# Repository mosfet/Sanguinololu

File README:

http://reprap.org/wiki/Sanguinololu

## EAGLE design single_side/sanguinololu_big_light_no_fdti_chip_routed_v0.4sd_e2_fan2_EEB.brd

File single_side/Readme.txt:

This is single side version of the board. 
-There are significant electrical changes
-12V needs to be distributed by thick jumper wires
-there are two GND bridges marked with red (top layer)
-serial jumper needs GND/power as jumper wires

features:
-large, single sided board designed for direct milling with f.e. "cyclone pcb factory"
-EEB (Extruder, Extruder, Bed) mosfet setup
-pwm on PB4 with bipolar key transistor for fan PWM (bd139)
-additional heater thermistor input
-built-in SD card reader header( for printing with auto0.g)
-removed FDTI - use esp8266 or just TTL serial cable instead, or bt module - designed with old android phone as display in mind
-there is i2c header for display and 3 pins left for encoder in case you Really need old clunky LCD
-additional E1 axis 
-better thermal design, large traces

TODO : 
-schematic needs tidy up actions. 
-untested yet. prints/etches ok with 0.22mm tool. 
-normalize drill sizes

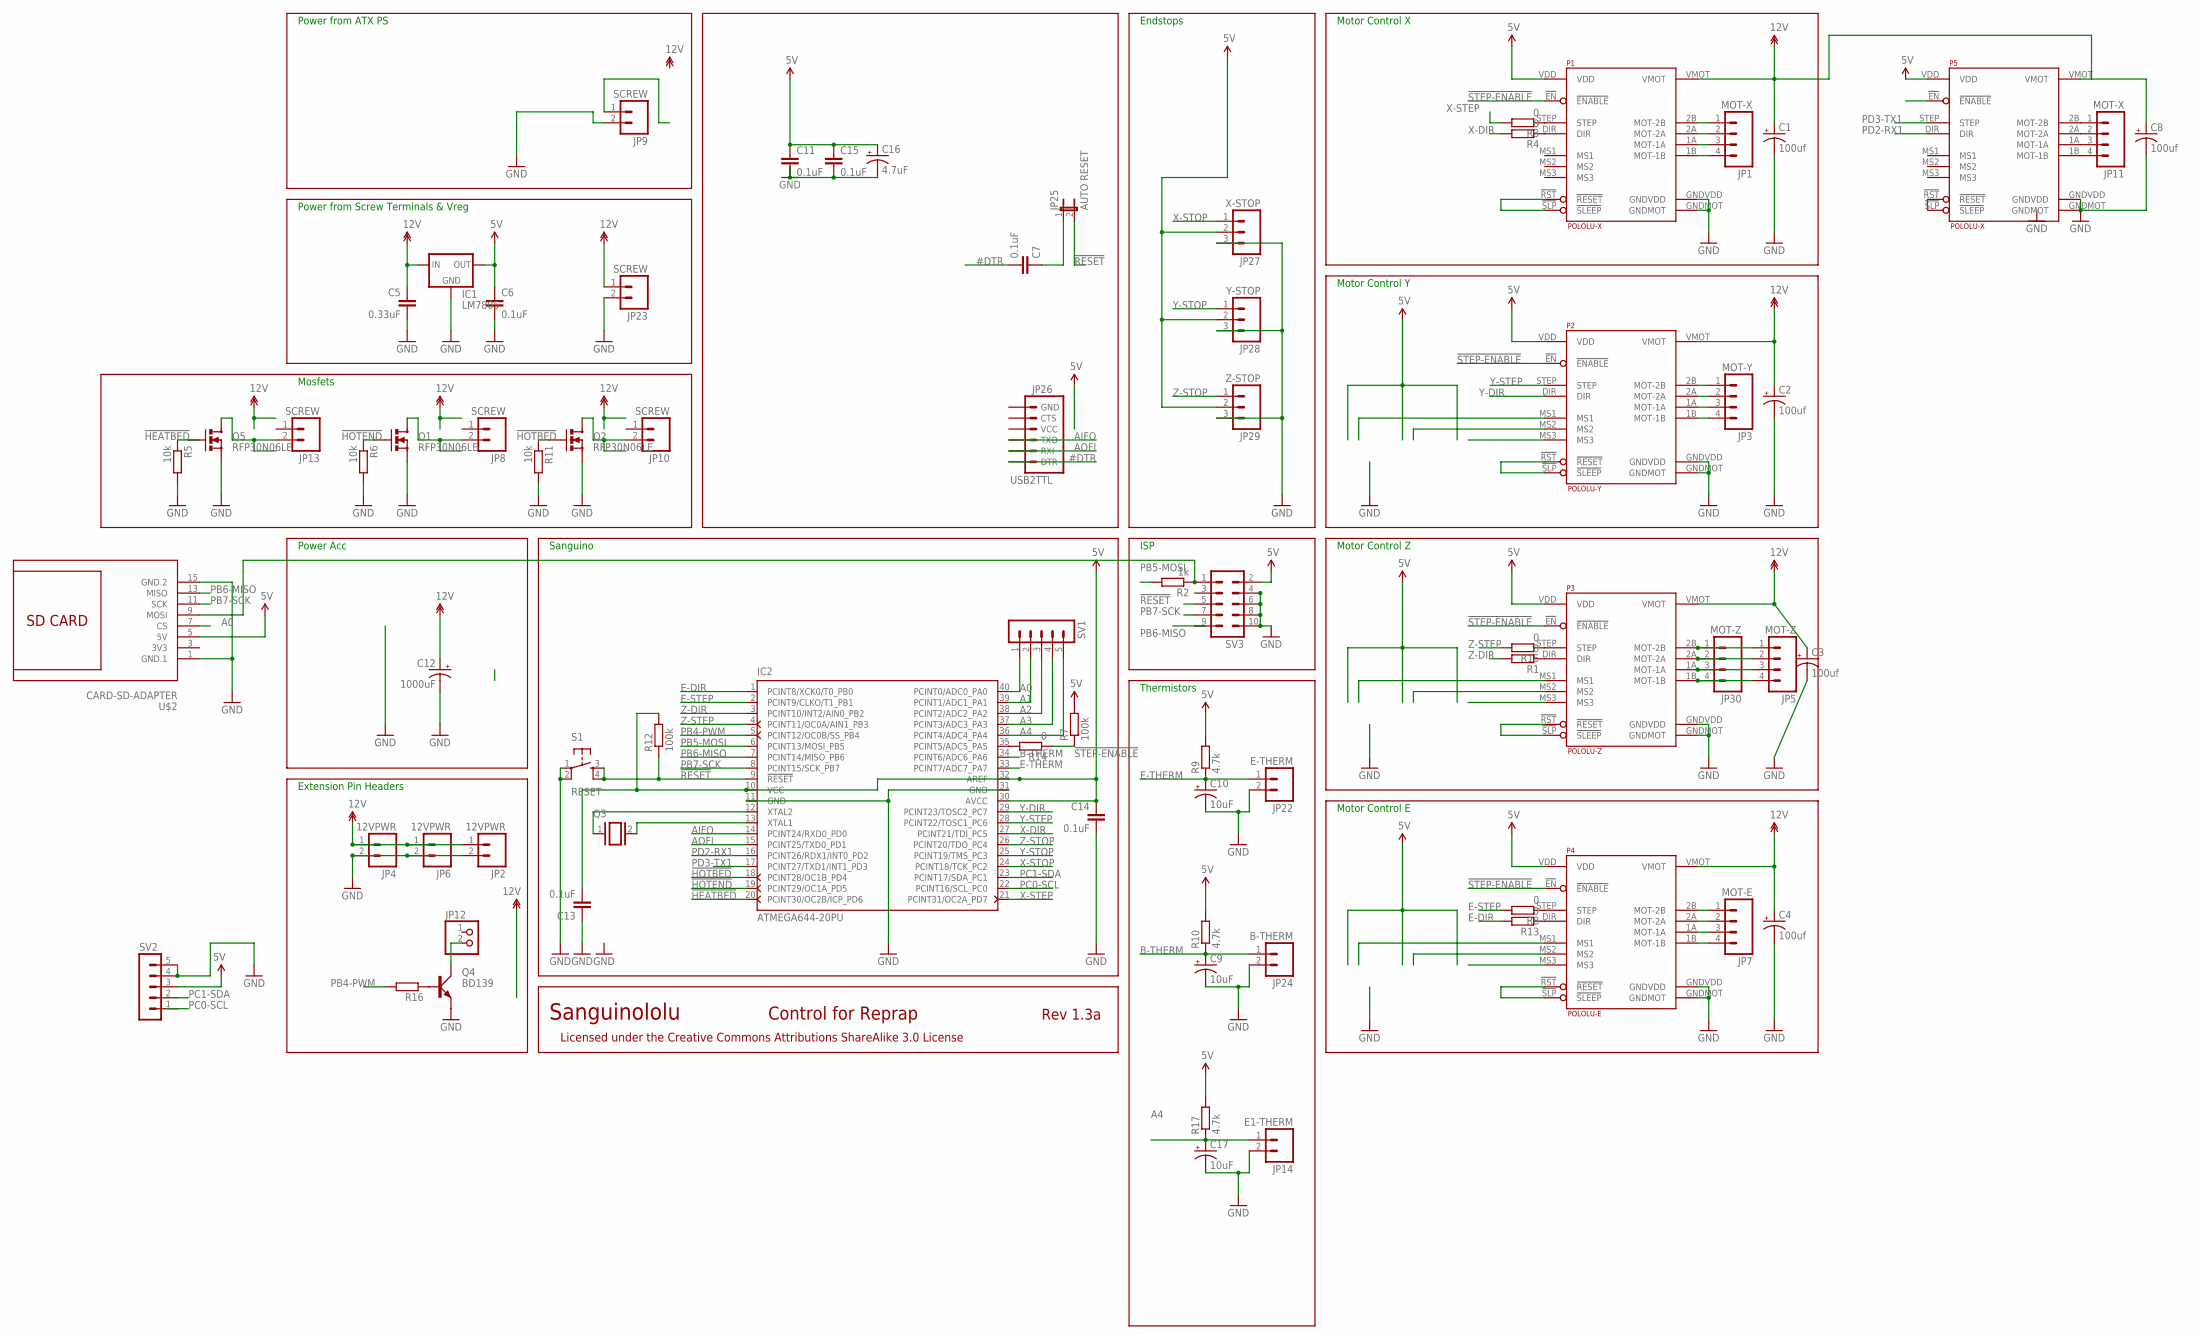
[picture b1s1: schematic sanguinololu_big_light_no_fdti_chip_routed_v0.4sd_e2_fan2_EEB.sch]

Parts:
C1, C2, C3, C4, C8: 100uf; CPOL-RADIAL-100UF-25V
C5: 0.33uF; CAP-PTH-SMALL2
C6, C13, C14: 0.1uF; CAP-PTH-SMALL2
C7: 0.1uF; C075-032X103
C9, C10, C17: 10uF; CPOL-RADIAL-10UF-25V
C11, C15: 0.1uF; C5B3
C12: 1000uF; CPOL-RADIAL-1000UF-25V
C16: 4.7uF; CPOL-RADIAL-10UF-25V
IC1: LM7805; 78XXL-CUSTOM
IC2: ATMEGA644-20PU; DIL40
JP1, JP11: MOT-X; MOLEX-1X4
JP2, JP4, JP6: 12VPWR; MOLEX-1X2
JP3: MOT-Y; MOLEX-1X4
JP5, JP30: MOT-Z; MOLEX-1X4
JP7: MOT-E; MOLEX-1X4
JP8, JP9, JP10, JP13, JP23: SCREW; SCREWTERMINAL-5MM-2
JP12: PINHD-1X2; 1X02
JP14: E1-THERM; 1X02
JP22: E-THERM; 1X02
JP24: B-THERM; 1X02
JP25: AUTO RESET; 1X02
JP26: USB2TTL; 1X06
JP27: X-STOP; MOLEX-1X3
JP28: Y-STOP; MOLEX-1X3
JP29: Z-STOP; MOLEX-1X3
P1, P5: POLOLU-X; POLOLU-ALLEGRO-PTH
P2: POLOLU-Y; POLOLU-ALLEGRO-PTH
P3: POLOLU-Z; POLOLU-ALLEGRO-PTH
P4: POLOLU-E; POLOLU-ALLEGRO-PTH
Q1, Q2, Q5: RFP30N06LE; TO220V
Q3: XTAL/S; QS
Q4: BD139; TO126AV
R1, R3, R4, R8, R13, R14, R15: 0; 0207/15
R2: 1k; 0207/15
R5, R6, R11: 10k; 0207/7
R7, R12: 100k; 0207/7
R9, R10, R17: 4.7k; 0207/7
R16: R-EU_0204/2V; 0204V
S1: RESET; TACTILE-PTH
SV1, SV2: MA05-1
SV3: MA05-2
U$2: CARD-SD-ADAPTER

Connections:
3V3: U$2.3 (3V3)
5V: C6.1, C11.1, C13.2, C14.1, C15.1, C16.1 (+), IC1.OUT, IC2.10 (VCC), IC2.30 (AVCC), IC2.32 (AREF), JP27.2, JP28.2, JP29.2, P1.VDD, P2.VDD, P3.VDD, P4.VDD, P5.VDD, R7.2, R9.2, R10.2, R12.2, R17.2, SV2.3, SV3.2, U$2.5 (5V)
12V: C1.1 (+), C2.1 (+), C3.1 (+), C4.1 (+), C5.1, C8.1 (+), C12.1 (+), IC1.IN, JP2.1, JP4.1, JP6.1, JP23.1, P1.VMOT, P2.VMOT, P3.VMOT, P4.VMOT, P5.VMOT
!FTDI-RESET: C7.1, JP25.1
!HEATBED: IC2.20 (PCINT30/OC2B/ICP_PD6), Q5.1 (G), R5.1
!HOTBED: IC2.18 (PCINT28/OC1B_PD4), Q2.1 (G), R11.1
!HOTEND: IC2.19 (PCINT29/OC1A_PD5), Q1.1 (G), R6.1
!RESET: IC2.9 (!RESET), JP25.2, R12.1, S1.3, S1.4, SV3.5
!STEP-ENABLE: P1.!EN (!ENABLE), P2.!EN (!ENABLE), P3.!EN (!ENABLE), P4.!EN (!ENABLE), P5.!EN (!ENABLE), R7.1, R14.1
#DTR: C7.2, JP26.1 (DTR)
A0: IC2.40 (PCINT0/ADC0_PA0), SV1.1, U$2.7 (CS)
A1: IC2.39 (PCINT1/ADC1_PA1), SV1.2
A2: IC2.38 (PCINT2/ADC2_PA2), SV1.3
A3: IC2.37 (PCINT3/ADC3_PA3), SV1.4
A4: C17.1 (+), IC2.36 (PCINT4/ADC4_PA4), JP14.1, R17.1, SV1.5
AIFO: IC2.14 (PCINT24/RXD0_PD0), JP26.3 (TXO)
AOFI: IC2.15 (PCINT25/TXD0_PD1), JP26.2 (RXI)
B-THERM: C9.1 (+), IC2.34 (PCINT6/ADC6_PA6), JP24.1, R10.1
E-DIR: IC2.1 (PCINT8/XCK0/T0_PB0), R13.2
E-MOT-1A: JP7.3, P4.1A (MOT-1A)
E-MOT-1B: JP7.4, P4.1B (MOT-1B)
E-MOT-2A: JP7.2, P4.2A (MOT-2A)
E-MOT-2B: JP7.1, P4.2B (MOT-2B)
E-MS1: P4.MS1
E-MS2: P4.MS2
E-MS3: P4.MS3
E-RESETSLEEP: P4.!RST (!RESET), P4.!SLP (!SLEEP)
E-STEP: IC2.2 (PCINT9/CLKO/T1_PB1), R8.2
E-THERM: C10.1 (+), IC2.33 (PCINT7/ADC7_PA7), JP22.1, R9.1
GND: C1.2 (-), C2.2 (-), C3.2 (-), C4.2 (-), C5.2, C6.2, C8.2 (-), C9.2 (-), C10.2 (-), C11.2, C12.2 (-), C13.1, C14.2, C15.2, C16.2 (-), C17.2 (-), IC1.GND, IC2.11 (GND), IC2.31 (GND), JP2.2, JP4.2, JP6.2, JP9.2, JP14.2, JP22.2, JP23.2, JP24.2, JP27.3, JP28.3, JP29.3, P1.GNDMOT, P1.GNDVDD, P2.GNDMOT, P2.GNDVDD, P3.GNDMOT, P3.GNDVDD, P4.GNDMOT, P4.GNDVDD, P5.GNDMOT, P5.GNDVDD, Q1.3 (S), Q2.3 (S), Q4.E, Q5.3 (S), R5.2, R6.2, R11.2, S1.1, S1.2, SV2.4, SV2.5, SV3.4, SV3.6, SV3.8, SV3.10, U$2.1 (GND.1), U$2.15 (GND.2)
HOTBED-GND: JP10.2, Q2.2 (D)
HOTEND-GND: JP8.2, Q1.2 (D)
HOTEND-GND1: JP13.2, Q5.2 (D)
unnamed: R2.1, SV3.1, U$2.9 (MOSI)
unnamed: P1.STEP, R3.1
unnamed: P1.DIR, R4.1
unnamed: P4.STEP, R8.1
unnamed: P4.DIR, R13.1
unnamed: IC2.12 (XTAL2), Q3.1
unnamed: IC2.13 (XTAL1), Q3.2
unnamed: IC2.35 (PCINT5/ADC5_PA5), R14.2
unnamed: P3.DIR, R1.1
unnamed: P3.STEP, R15.1
unnamed: JP11.1, P5.2B (MOT-2B)
unnamed: JP11.2, P5.2A (MOT-2A)
unnamed: JP11.3, P5.1A (MOT-1A)
unnamed: JP11.4, P5.1B (MOT-1B)
unnamed: P5.!RST (!RESET), P5.!SLP (!SLEEP)
unnamed: JP12.2, Q4.C
unnamed: Q4.B, R16.1
PB4-PWM: IC2.5 (PCINT12/OC0B/SS_PB4), R16.2
PB5-MOSI: IC2.6 (PCINT13/MOSI_PB5), R2.2
PB6-MISO: IC2.7 (PCINT14/MISO_PB6), SV3.9, U$2.13 (MISO)
PB7-SCK: IC2.8 (PCINT15/SCK_PB7), SV3.7, U$2.11 (SCK)
PC0-SCL: IC2.22 (PCINT16/SCL_PC0), SV2.1
PC1-SDA: IC2.23 (PCINT17/SDA_PC1), SV2.2
PD2-RX1: IC2.16 (PCINT26/RDX1/INT0_PD2), P5.DIR
PD3-TX1: IC2.17 (PCINT27/TXD1/INT1_PD3), P5.STEP
X-DIR: IC2.27 (PCINT21/TDI_PC5), R4.2
X-MOT-1A: JP1.3, P1.1A (MOT-1A)
X-MOT-1B: JP1.4, P1.1B (MOT-1B)
X-MOT-2A: JP1.2, P1.2A (MOT-2A)
X-MOT-2B: JP1.1, P1.2B (MOT-2B)
X-RESETSLEEP: P1.!RST (!RESET), P1.!SLP (!SLEEP)
X-STEP: IC2.21 (PCINT31/OC2A_PD7), R3.2
X-STOP: IC2.24 (PCINT18/TCK_PC2), JP27.1
Y-DIR: IC2.29 (PCINT23/TOSC2_PC7), P2.DIR
Y-MOT-1A: JP3.3, P2.1A (MOT-1A)
Y-MOT-1B: JP3.4, P2.1B (MOT-1B)
Y-MOT-2A: JP3.2, P2.2A (MOT-2A)
Y-MOT-2B: JP3.1, P2.2B (MOT-2B)
Y-MS1: P2.MS1
Y-MS2: P2.MS2
Y-MS3: P2.MS3
Y-RESETSLEEP: P2.!RST (!RESET), P2.!SLP (!SLEEP)
Y-STEP: IC2.28 (PCINT22/TOSC1_PC6), P2.STEP
Y-STOP: IC2.25 (PCINT19/TMS_PC3), JP28.1
Z-DIR: IC2.3 (PCINT10/INT2/AIN0_PB2), R1.2
Z-MOT-1A: JP5.3, JP30.3, P3.1A (MOT-1A)
Z-MOT-1B: JP5.4, JP30.4, P3.1B (MOT-1B)
Z-MOT-2A: JP5.2, JP30.2, P3.2A (MOT-2A)
Z-MOT-2B: JP5.1, JP30.1, P3.2B (MOT-2B)
Z-MS1: P3.MS1
Z-MS2: P3.MS2
Z-MS3: P3.MS3
Z-RESETSLEEP: P3.!RST (!RESET), P3.!SLP (!SLEEP)
Z-STEP: IC2.4 (PCINT11/OC0A/AIN1_PB3), R15.2
Z-STOP: IC2.26 (PCINT20/TDO_PC4), JP29.1

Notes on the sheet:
Motor Control X
Motor Control Y
Motor Control Z
Motor Control E
ISP
Thermistors
Endstops
Sanguino
Mosfets
Power Acc
Sanguinololu
Rev 1.3a
Control for Reprap
Licensed under the Creative Commons Attributions ShareAlike 3.0 License
Extension Pin Headers
Power from ATX PS
Power from Screw Terminals & Vreg

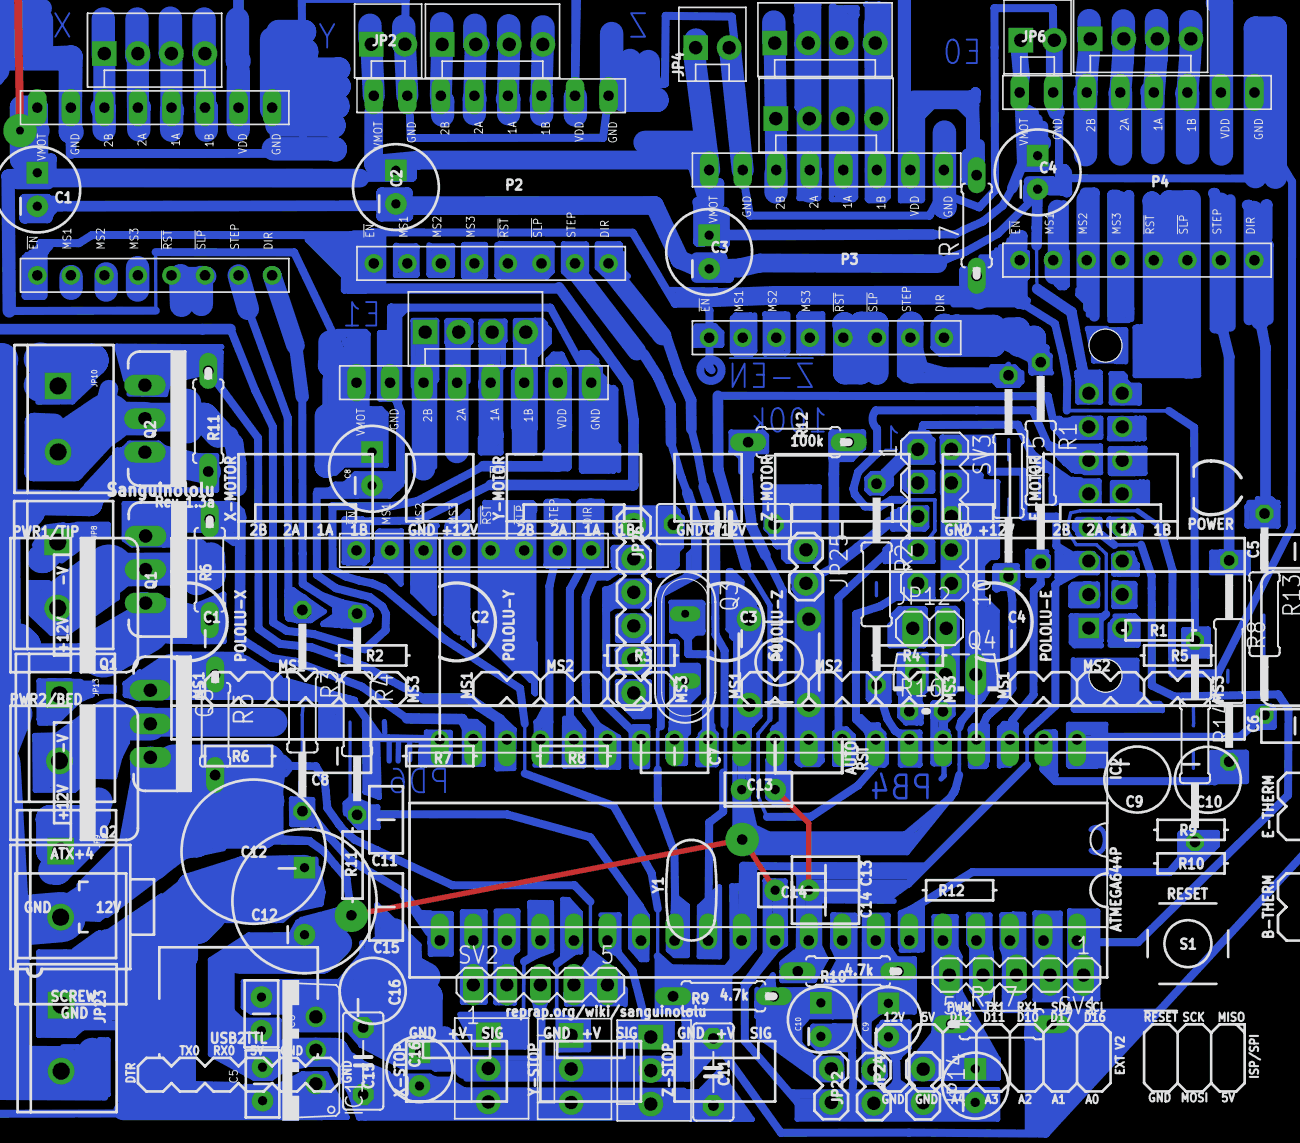
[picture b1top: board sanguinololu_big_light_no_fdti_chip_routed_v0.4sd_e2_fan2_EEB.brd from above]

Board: 2 copper layers, 74 parts (1 on the bottom side), 78 nets.

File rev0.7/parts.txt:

Vreg kit
  IC1       LM7805          
  JP23     SCREW            5MM 2P
  C5       0.33uF           ML CERAMIC
  C6       0.1uF            ML CERAMIC

Atx connector kit
  ATX1     ATX-4VERTICAL    ATX-4VERTICAL
  HDDPWR   5v/12v           MOLE DRIVEPWRVERTICAL

Ftdi kit
  IC100    FT232RL          FT232RLSSOP
  J1       USB              USB PTH R/A
  C16      4.7uF            POLARIZED 25V
  C11      0.1uF            ML CERAMIC
  C15      0.1uF            ML CERAMIC
  C7       0.1uF            ML CERAMIC
  C8       0.1uF            ML CERAMIC

Core kit:
  IC2      ATMEGA644-20PU   
  IC2-2    DIP-40 OPEN FRAME SOCKET
  
  LED1     POWER            LED3MM
  
  Y1       16MHz 22pF       RESONATORPTH
  
  S1       RESET            TAC_SWITCHPTH
  
  Q1       RFP30N06LE       MOSFET-NCHANNELPTH2
  Q2       RFP30N06LE       MOSFET-NCHANNELPTH2

  electrolytic capacitors:
  C12      1000uF           POLARIZED 35V
  
  C1       100uf            POLARIZED 35V
  C2       100uf            POLARIZED 35V
  C3       100uf            POLARIZED 35V
  C4       100uf            POLARIZED 35V
  
  C9       10uF             POLARIZED 35V
  C10      10uF             POLARIZED 35V
  
  ceramic capacitors:
  C13      0.1uF            ML CERAMIC
  C14      0.1uF            ML CERAMIC
  
  resistors:
  R2       100k             
  R3       100k             
  R4       100k             
  R5       100k             
  R12      100k             
  
  R11      10k              
  R6       10k              
  
  R9       4.7k             
  R10      4.7k             
  
  R1       1.5k             
  
  R7       1k               
  R8       1k               
  
  female headers - each requires qty two 8 pin female header:
  P1       POLOLU-X         
  P2       POLOLU-Y         
  P3       POLOLU-Z         
  P4       POLOLU-E         

  male 4pin header - qty six:
  JP1      MOT-X
  JP3      MOT-Y
  JP5      MOT-Z
  JP7      MOT-E
  JP8      HOTEND
  JP21     HOTBED
  
  male 3pin header - qty three:
  JP27     X-STOP
  JP28     Y-STOP
  JP29     Z-STOP
  
  male 2pin header - qty five:
  JP22     E-THERM
  JP24     B-THERM
  JP2      12VPWR
  JP4      12VPWR
  JP6      12VPWR
  
  male 2pin VERTICAL ONLY header - qty twelve, also get qty twelve shunts:
  JP9      X-MS1
  JP10     X-MS2
  JP11     X-MS3
  JP12     Y-MS1
  JP13     Y-MS2
  JP14     Y-MS3
  JP15     Z-MS1
  JP16     Z-MS2
  JP17     Z-MS3
  JP18     E-MS1
  JP19     E-MS2
  JP20     E-MS3
  
  optional / no part footprints
  SJ100    5v/12v SOLDERJUMPBER
  JP26     USB2TTL 6 PIN 
  U$24     EXPANSION 2x8 and 2x3 w/ PLATED-SCREW
  U$17     PLATED-SCREW
  U$37     PLATED-SCREW
  U$38     PLATED-SCREW

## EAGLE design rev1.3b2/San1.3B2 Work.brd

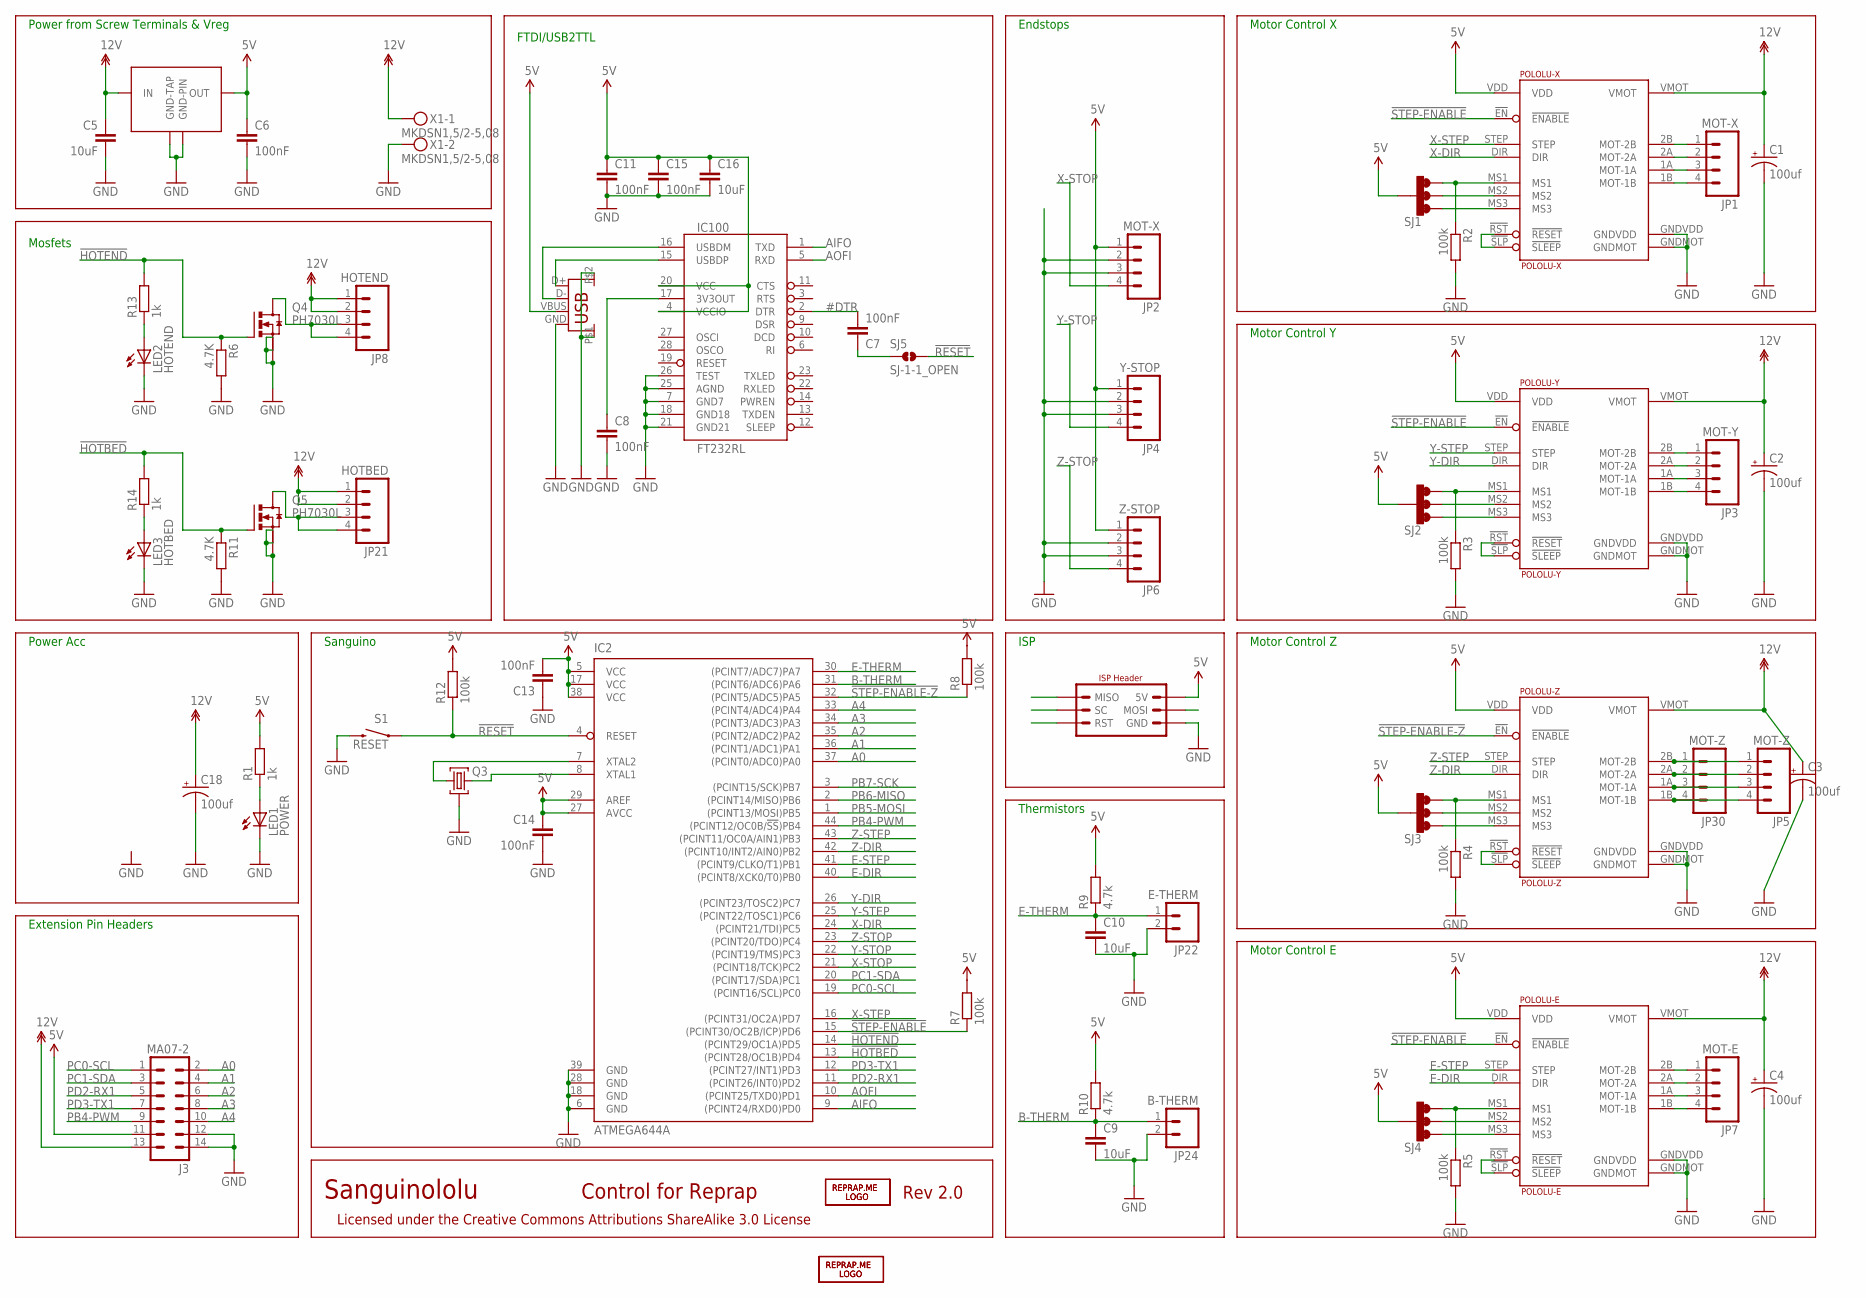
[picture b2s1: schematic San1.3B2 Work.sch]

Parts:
C1, C2, C3, C4, C18: 100uf; PANASONIC_D
C5, C9, C10, C16: 10uF; C1206
C6, C7, C8, C11, C13, C14, C15: 100nF; 0805
IC1: V-REG+; TO252+EXTRA-PIN
IC2: ATMEGA644A; TQFP44
IC100: FT232RL; SSOP28DB
J1: USB; USB-B-PTH
J2: ISP-HEADER
J3: MA07-2
JP1, JP2: MOT-X; MOLEX-1X4
JP3: MOT-Y; MOLEX-1X4
JP4: Y-STOP; MOLEX-1X4
JP5, JP30: MOT-Z; MOLEX-1X4
JP6: Z-STOP; MOLEX-1X4
JP7: MOT-E; MOLEX-1X4
JP8: HOTEND; MOLEX-1X4_NO_THERMAL
JP21: HOTBED; MOLEX-1X4_NO_THERMAL
JP22: E-THERM; 1X02
JP24: B-THERM; 1X02
LED1: POWER; CHIP-LED0805
LED2: HOTEND; CHIP-LED0805
LED3: HOTBED; CHIP-LED0805
LOGO1, LOGO2: REPRAP-LOGO6X100_BOTSILK; REPRAP.ME_6X100_BOTSILK
LOGO3, LOGO4: REPRAP-LOGO6X100_TOPSILK; REPRAP.ME_6X100_TOPSILK
POLOLU-E: POLOLU-E; POLOLU-ALLEGRO-PTH
POLOLU-X: POLOLU-X; POLOLU-ALLEGRO-PTH
POLOLU-Y: POLOLU-Y; POLOLU-ALLEGRO-PTH
POLOLU-Z: POLOLU-Z; POLOLU-ALLEGRO-PTH
Q3: AWSCR-CV; AWSCR
Q4, Q5: PH7030L; SOT669-NO-THERMAL
R1, R13, R14: 1k; R0805
R2, R3, R4, R5, R7, R8, R12: 100k; R0805
R6, R11: 4.7K; R0805
R9, R10: 4.7k; R0805
S1: RESET; TACTILE_SWITCH_TALL
SJ1, SJ2, SJ3, SJ4: SJ-3
SJ5: SJ-1-1_OPEN
X1: MKDSN1,5/2-5,08

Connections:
3V3: C8.1, IC100.17 (3V3OUT)
5V: C6.1, C11.1, C13.2, C14.1, C15.1, C16.1, IC1.2 (OUT), IC2.5 (VCC), IC2.17 (VCC), IC2.27 (AVCC), IC2.29 (AREF), IC2.38 (VCC), IC100.4 (VCCIO), IC100.20 (VCC), J1.VBUS, J2.2 (5V), J3.11, JP2.1, JP4.1, JP6.1, POLOLU-E.VDD, POLOLU-X.VDD, POLOLU-Y.VDD, POLOLU-Z.VDD, R1.2, R7.2, R8.2, R9.2, R10.2, R12.2, SJ1.4 (COMMON), SJ2.4 (COMMON), SJ3.4 (COMMON), SJ4.4 (COMMON)
12V: C1.+, C2.+, C3.+, C4.+, C5.1, C18.+, IC1.1 (IN), J3.13, JP8.1, JP8.2, JP21.1, JP21.2, POLOLU-E.VMOT, POLOLU-X.VMOT, POLOLU-Y.VMOT, POLOLU-Z.VMOT, X1.1
!FTDI-RESET: C7.1, SJ5.1
!HOTBED: IC2.13 ((PCINT28/OC1B)PD4), Q5.4 (G), R11.1, R14.2
!HOTEND: IC2.14 ((PCINT29/OC1A)PD5), Q4.4 (G), R6.1, R13.2
!RESET: IC2.4 (RESET), J2.5 (RST), R12.1, S1.A2 (1), SJ5.2
!STEP-ENABLE: IC2.15 ((PCINT30/OC2B/ICP)PD6), POLOLU-E.!EN (!ENABLE), POLOLU-X.!EN (!ENABLE), POLOLU-Y.!EN (!ENABLE), R7.1
!STEP-ENABLE-Z: IC2.32 ((PCINT5/ADC5)PA5), POLOLU-Z.!EN (!ENABLE), R8.1
#DTR: C7.2, IC100.2 (DTR)
A0: IC2.37 ((PCINT0/ADC0)PA0), J3.2
A1: IC2.36 ((PCINT1/ADC1)PA1), J3.4
A2: IC2.35 ((PCINT2/ADC2)PA2), J3.6
A3: IC2.34 ((PCINT3/ADC3)PA3), J3.8
A4: IC2.33 ((PCINT4/ADC4)PA4), J3.10
AIFO: IC2.9 ((PCINT24/RXD0)PD0), IC100.1 (TXD)
AOFI: IC2.10 ((PCINT25/TXD0)PD1), IC100.5 (RXD)
B-THERM: C9.1, IC2.31 ((PCINT6/ADC6)PA6), JP24.1, R10.1
E-DIR: IC2.40 ((PCINT8/XCK0/T0)PB0), POLOLU-E.DIR
E-MOT-1A: JP7.3, POLOLU-E.1A (MOT-1A)
E-MOT-1B: JP7.4, POLOLU-E.1B (MOT-1B)
E-MOT-2A: JP7.2, POLOLU-E.2A (MOT-2A)
E-MOT-2B: JP7.1, POLOLU-E.2B (MOT-2B)
E-MS1: POLOLU-E.MS1, R5.1, SJ4.3
E-MS2: POLOLU-E.MS2, SJ4.2
E-MS3: POLOLU-E.MS3, SJ4.1
E-RESETSLEEP: POLOLU-E.!RST (!RESET), POLOLU-E.!SLP (!SLEEP)
E-STEP: IC2.41 ((PCINT9/CLKO/T1)PB1), POLOLU-E.STEP
E-THERM: C10.1, IC2.30 ((PCINT7/ADC7)PA7), JP22.1, R9.1
GND: C1.-, C2.-, C3.-, C4.-, C5.2, C6.2, C8.2, C9.2, C10.2, C11.2, C13.1, C14.2, C15.2, C16.2, C18.-, IC1.3 (GND-TAP), IC1.4 (GND-PIN), IC2.6 (GND), IC2.18 (GND), IC2.28 (GND), IC2.39 (GND), IC100.7 (GND7), IC100.18 (GND18), IC100.21 (GND21), IC100.25 (AGND), IC100.26 (TEST), J1.GND, J1.P$1, J1.P$2, J2.6 (GND), J3.12, J3.14, JP2.2, JP2.3, JP4.2, JP4.3, JP6.2, JP6.3, JP22.2, JP24.2, LED1.C, LED2.C, LED3.C, POLOLU-E.GNDMOT, POLOLU-E.GNDVDD, POLOLU-X.GNDMOT, POLOLU-X.GNDVDD, POLOLU-Y.GNDMOT, POLOLU-Y.GNDVDD, POLOLU-Z.GNDMOT, POLOLU-Z.GNDVDD, Q3.GND (2), Q4.1 (S), Q4.2 (S), Q4.3 (S), Q5.1 (S), Q5.2 (S), Q5.3 (S), R2.2, R3.2, R4.2, R5.2, R6.2, R11.2, S1.B2 (2), X1.2
HOTBED-GND: JP21.3, JP21.4, Q5.MB (D)
HOTEND-GND: JP8.3, JP8.4, Q4.MB (D)
LED1: LED1.A, R1.1
LED2: LED2.A, R13.1
LED3: LED3.A, R14.1
unnamed: IC2.8 (XTAL1), Q3.IN (3)
unnamed: IC2.7 (XTAL2), Q3.OUT (1)
PB4-PWM: IC2.44 ((PCINT12/OC0B/!SS!)PB4), J3.9
PB5-MOSI: IC2.1 ((PCINT13/MOSI)PB5), J2.4 (MOSI)
PB6-MISO: IC2.2 ((PCINT14/MISO)PB6), J2.1 (MISO)
PB7-SCK: IC2.3 ((PCINT15/SCK)PB7), J2.3 (SC)
PC0-SCL: IC2.19 ((PCINT16/SCL)PC0), J3.1
PC1-SDA: IC2.20 ((PCINT17/SDA)PC1), J3.3
PD2-RX1: IC2.11 ((PCINT26/INT0)PD2), J3.5
PD3-TX1: IC2.12 ((PCINT27/INT1)PD3), J3.7
USBDM: IC100.16 (USBDM), J1.D-
USBDP: IC100.15 (USBDP), J1.D+
X-DIR: IC2.24 ((PCINT21/TDI)PC5), POLOLU-X.DIR
X-MOT-1A: JP1.3, POLOLU-X.1A (MOT-1A)
X-MOT-1B: JP1.4, POLOLU-X.1B (MOT-1B)
X-MOT-2A: JP1.2, POLOLU-X.2A (MOT-2A)
X-MOT-2B: JP1.1, POLOLU-X.2B (MOT-2B)
X-MS1: POLOLU-X.MS1, R2.1, SJ1.3
X-MS2: POLOLU-X.MS2, SJ1.2
X-MS3: POLOLU-X.MS3, SJ1.1
X-RESETSLEEP: POLOLU-X.!RST (!RESET), POLOLU-X.!SLP (!SLEEP)
X-STEP: IC2.16 ((PCINT31/OC2A)PD7), POLOLU-X.STEP
X-STOP: IC2.21 ((PCINT18/TCK)PC2), JP2.4
Y-DIR: IC2.26 ((PCINT23/TOSC2)PC7), POLOLU-Y.DIR
Y-MOT-1A: JP3.3, POLOLU-Y.1A (MOT-1A)
Y-MOT-1B: JP3.4, POLOLU-Y.1B (MOT-1B)
Y-MOT-2A: JP3.2, POLOLU-Y.2A (MOT-2A)
Y-MOT-2B: JP3.1, POLOLU-Y.2B (MOT-2B)
Y-MS1: POLOLU-Y.MS1, R3.1, SJ2.3
Y-MS2: POLOLU-Y.MS2, SJ2.2
Y-MS3: POLOLU-Y.MS3, SJ2.1
Y-RESETSLEEP: POLOLU-Y.!RST (!RESET), POLOLU-Y.!SLP (!SLEEP)
Y-STEP: IC2.25 ((PCINT22/TOSC1)PC6), POLOLU-Y.STEP
Y-STOP: IC2.22 ((PCINT19/TMS)PC3), JP4.4
Z-DIR: IC2.42 ((PCINT10/INT2/AIN0)PB2), POLOLU-Z.DIR
Z-MOT-1A: JP5.3, JP30.3, POLOLU-Z.1A (MOT-1A)
Z-MOT-1B: JP5.4, JP30.4, POLOLU-Z.1B (MOT-1B)
Z-MOT-2A: JP5.2, JP30.2, POLOLU-Z.2A (MOT-2A)
Z-MOT-2B: JP5.1, JP30.1, POLOLU-Z.2B (MOT-2B)
Z-MS1: POLOLU-Z.MS1, R4.1, SJ3.3
Z-MS2: POLOLU-Z.MS2, SJ3.2
Z-MS3: POLOLU-Z.MS3, SJ3.1
Z-RESETSLEEP: POLOLU-Z.!RST (!RESET), POLOLU-Z.!SLP (!SLEEP)
Z-STEP: IC2.43 ((PCINT11/OC0A/AIN1)PB3), POLOLU-Z.STEP
Z-STOP: IC2.23 ((PCINT20/TDO)PC4), JP6.4

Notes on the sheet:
Motor Control X
Motor Control Y
Motor Control Z
Motor Control E
ISP
Thermistors
Endstops
Sanguino
FTDI/USB2TTL
Mosfets
Power Acc
Sanguinololu
Rev 2.0
Control for Reprap
Licensed under the Creative Commons Attributions ShareAlike 3.0 License
Extension Pin Headers
Power from Screw Terminals & Vreg

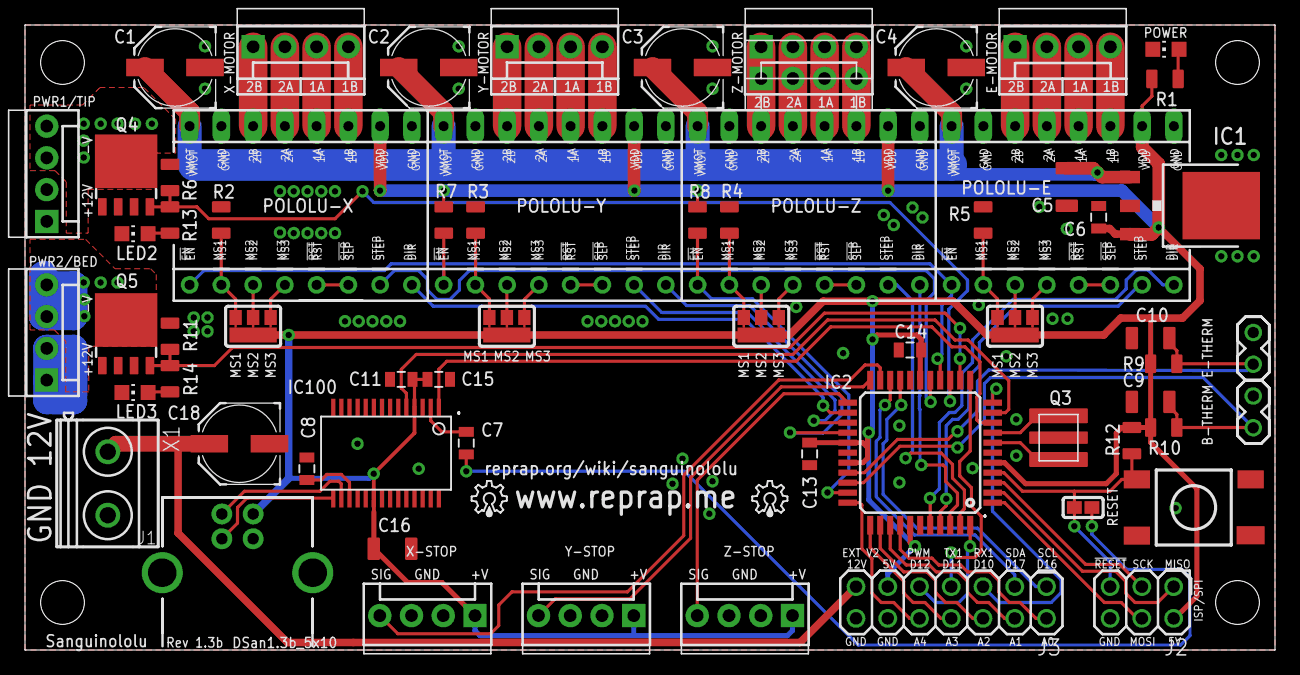
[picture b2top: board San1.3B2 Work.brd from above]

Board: 2 copper layers, 100.0 x 50.0 mm, 69 parts (0 on the bottom side), 80 nets.

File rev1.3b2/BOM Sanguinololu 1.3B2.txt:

Partlist

Exported from San1.3B2 Work.brd at 20-03-2014 21:55:24

EAGLE Version 6.1.0 Copyright (c) 1988-2012 CadSoft

Assembly variant: 

Part     Value           Package              Library         Position (mm)         Orientation

C1       100uf           PANASONIC_D          SparkFun        (12 46.6)             R180
C2       100uf           PANASONIC_D          SparkFun        (32.3 46.6)           R180
C3       100uf           PANASONIC_D          SparkFun        (52.6 46.6)           R180
C4       100uf           PANASONIC_D          SparkFun        (72.9 46.6)           R180
C5       10uF            C1206                REPRAP_ME       (83.345 37.04)        R270
C6       100nF           0805                 SparkFun        (85.894 34.62)        R90
C7       100nF           0805                 SparkFun        (35.3 16.55)          R90
C8       100nF           0805                 SparkFun        (22.55 14.5)          R90
C9       10uF            C1206                REPRAP_ME       (90.05 19.85)         R180
C10      10uF            C1206                REPRAP_ME       (90.05 24.95)         R180
C11      100nF           0805                 SparkFun        (30.1 21.65)          R180
C13      100nF           0805                 SparkFun        (62.77 15.69)         R90
C14      100nF           0805                 SparkFun        (70.8 24)             R180
C15      100nF           0805                 SparkFun        (33.1 21.65)          R0
C16      10uF            C1206                REPRAP_ME       (29.4 8.1)            R0
C18      100uf           PANASONIC_D          SparkFun        (17.15 16.5)          R180
IC1      V-REG+          TO252+EXTRA-PIN      REPRAP_ME       (93.2 35.55)          R270
IC2      ATMEGA644A      TQFP44               atmel           (71.61464375 15.785353125) R180
IC100    FT232RL         SSOP28DB             SparkFun        (28.885 15.75)        R180
J1       USB             USB-B-PTH            SparkFun        (17 8.9)              R90
J2                       ISP-HEADER           REPRAP_ME       (89.35 3.8)           R180
J3       MA07-2          MA07-2               Header Male     (74.1 3.8)            R180
JP1      MOT-X           MOLEX-1X4            SparkFun        (18.25 48.26)         R0
JP2      MOT-X           MOLEX-1X4            SparkFun        (36 2.75)             R180
JP3      MOT-Y           MOLEX-1X4            SparkFun        (38.57 48.26)         R0
JP4      Y-STOP          MOLEX-1X4            SparkFun        (48.7 2.75)           R180
JP5      MOT-Z           MOLEX-1X4            SparkFun        (58.89 48.26)         R0
JP6      Z-STOP          MOLEX-1X4            SparkFun        (61.4 2.75)           R180
JP7      MOT-E           MOLEX-1X4            SparkFun        (79.21 48.26)         R0
JP8      HOTEND          MOLEX-1X4_NO_THERMAL REPRAP_ME       (1.74 34.29)          R90
JP21     HOTBED          MOLEX-1X4_NO_THERMAL REPRAP_ME       (1.74 21.59)          R90
JP22     E-THERM         1X02                 SparkFun        (98.26 22.86)         R90
JP24     B-THERM         1X02                 SparkFun        (98.26 17.78)         R90
JP30     MOT-Z           MOLEX-1X4            SparkFun        (58.89 45.72)         R0
LED1     POWER           CHIP-LED0805         led             (91.275 48.06)        R90
LED2     HOTEND          CHIP-LED0805         led             (8.8 33.3)            R90
LED3     HOTBED          CHIP-LED0805         led             (8.8 20.6)            R90
POLOLU-E POLOLU-E        POLOLU-ALLEGRO-PTH   pololu-allegro  (83.02 35.56)         R90
POLOLU-X POLOLU-X        POLOLU-ALLEGRO-PTH   pololu-allegro  (22.06 35.56)         R90
POLOLU-Y POLOLU-Y        POLOLU-ALLEGRO-PTH   pololu-allegro  (42.38 35.56)         R90
POLOLU-Z POLOLU-Z        POLOLU-ALLEGRO-PTH   pololu-allegro  (62.7 35.56)          R90
Q3                       AWSCR                REPRAP_ME       (82.68485 16.987434375) R270
Q4       PH7030L         SOT669-NO-THERMAL    REPRAP_ME       (8.09 38.1)           R0
Q5       PH7030L         SOT669-NO-THERMAL    REPRAP_ME       (8.09 25.4)           R0
R1       1k              R0805                REPRAP_ME       (91.2 45.685)         R180
R2       100k            R0805                REPRAP_ME       (15.7 34.4)           R90
R3       100k            R0805                REPRAP_ME       (36.05 34.4)          R90
R4       100k            R0805                REPRAP_ME       (56.35 34.4)          R90
R5       100k            R0805                REPRAP_ME       (76.65 34.4)          R90
R6       4.7K            R0805                REPRAP_ME       (11.6 37.8)           R90
R7       100k            R0805                REPRAP_ME       (33.5 34.4)           R90
R8       100k            R0805                REPRAP_ME       (53.8 34.4)           R90
R9       4.7k            R0805                REPRAP_ME       (91.1 22.9)           R180
R10      4.7k            R0805                REPRAP_ME       (91.1 17.8)           R180
R11      4.7K            R0805                REPRAP_ME       (11.6 25.1)           R90
R12      100k            R0805                REPRAP_ME       (88.55 16.75)         R90
R13      1k              R0805                REPRAP_ME       (11.6 34.4)           R90
R14      1k              R0805                REPRAP_ME       (11.6 21.7)           R90
S1       RESET           TACTILE_SWITCH_TALL  printrbot       (93.5 11.4)           R180
SJ1                      SJ-3                 REPRAP_ME       (18.25 25.9)          R180
SJ2                      SJ-3                 REPRAP_ME       (38.55 25.9)          R180
SJ3                      SJ-3                 REPRAP_ME       (58.9 25.9)           R180
SJ4                      SJ-3                 REPRAP_ME       (79.2 25.9)           R180
SJ5      SJ-1-1_OPEN     SJ-1-1_OPEN          REPRAP_ME       (84.65 11.4)          R270
X1       MKDSN1,5/2-5,08 MKDSN1,5/2-5,08      con-phoenix-508 (6.6 13.3)            R270

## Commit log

2011-03-04 Initial checkin of finalized and working revisions
2011-03-04 Initial commit of readme
2011-03-04 added photos and images
2011-03-05 added images for usb fix on rev 0.6, updated working rev 0.7 with comments from mail & thread
2011-03-06 improved routing, reduced number of vias
2011-03-07 checkin for maxbots
2011-03-07 realign mounting holes to mm grid
2011-03-07 made space on hdd connector side
2011-03-08 updated library with plated screw terminal package, added this to sanguinololu board
2011-03-10 update to gnd
2011-03-12 finalized rev0.7, generated gerber files
2011-03-12 added rev1.0-working from 0.7 final
2011-03-13 added images
2011-03-13 updated psd file location
2011-03-13 added parts list
2011-03-22 lots of little changes, plus became in compliance with a much stricter design rules dru file
2011-03-24 *Ready for Production* finalized 1.0: rotated screw terminal to face off nearest edge, tighter drc rules ( 10 mil width, spacing, 20 mil drill & 20 mil annular ) generated gerber files
    there will be no further changes to this version
2011-04-08 added parts list, fixed a trace length, this is the final checkin for 1.0
2011-04-08 added gerbers, this is the final checkin for 1.0
2011-04-08 updated to 35v, ok THIS one is the final checkin...
2011-04-19 check in v 1.1 final
2011-04-25 rename gerber file
2011-05-19 Core type changed from 644 to 644P (which is the Sanguino)
2011-05-24 added v 1.2
2011-05-30 forgot the schematic
2011-06-15 added images, updated library
2011-06-16 checkin 1.3 for WebSpider
2011-06-16 added 2nd z conenctor
2011-06-16 fix silkscreen for z-two
2011-06-30 checkin 1.3a
2014-08-20 Revision 1.3b2
    Mostly SMD for easier production workflow
2018-03-28 single side board for easy DIY manufacture
2018-03-29 EEB version gerber files
2018-04-14 beefed up the tracks and soldering pads

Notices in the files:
parts and their libraries:
sd_adapter_full: Released under the Creative Commons Attribution 4.0 International License: http://creativecommons.org/licenses/by/4.0
